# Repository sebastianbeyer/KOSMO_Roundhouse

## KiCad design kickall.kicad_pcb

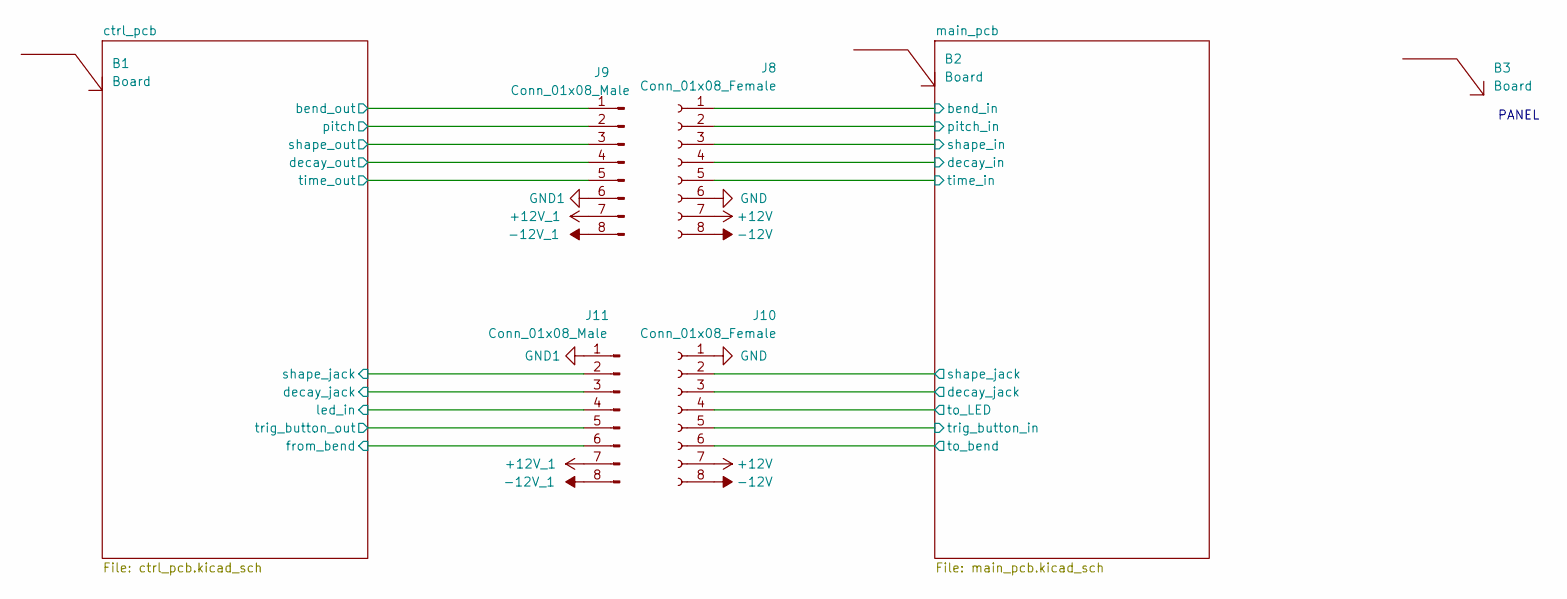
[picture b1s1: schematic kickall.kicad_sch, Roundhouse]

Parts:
B1, B2, B3: Board; Board_Marker
J8, J10: Conn_01x08_Female; PinSocket_1x08_P2.54mm_Vertical
J9, J11: Conn_01x08_Male; PinHeader_1x08_P2.54mm_Vertical

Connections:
+12V: J8.7, J10.7; also elsewhere on the board
+12V_1: J9.7, J11.7; also elsewhere on the board
-12V: J8.8, J10.8; also elsewhere on the board
-12V_1: J9.8, J11.8; also elsewhere on the board
/ctrl_pcb/bend_out: J9.1; also elsewhere on the board
/ctrl_pcb/decay_jack: J11.3; also elsewhere on the board
/ctrl_pcb/decay_out: J9.4; also elsewhere on the board
/ctrl_pcb/from_bend: J11.6; also elsewhere on the board
/ctrl_pcb/led_in: J11.4; also elsewhere on the board
/ctrl_pcb/pitch: J9.2; also elsewhere on the board
/ctrl_pcb/shape_jack: J11.2; also elsewhere on the board
/ctrl_pcb/shape_out: J9.3; also elsewhere on the board
/ctrl_pcb/time_out: J9.5; also elsewhere on the board
/ctrl_pcb/trig_button_out: J11.5; also elsewhere on the board
/main_pcb/bend_in: J8.1; also elsewhere on the board
/main_pcb/decay_in: J8.4; also elsewhere on the board
/main_pcb/decay_jack: J10.3; also elsewhere on the board
/main_pcb/pitch_in: J8.2; also elsewhere on the board
/main_pcb/shape_in: J8.3; also elsewhere on the board
/main_pcb/shape_jack: J10.2; also elsewhere on the board
/main_pcb/time_in: J8.5; also elsewhere on the board
/main_pcb/to_LED: J10.4; also elsewhere on the board
/main_pcb/to_bend: J10.6; also elsewhere on the board
/main_pcb/trig_button_in: J10.5; also elsewhere on the board
GND: J8.6, J10.1; also elsewhere on the board
GND1: J9.6, J11.1; also elsewhere on the board

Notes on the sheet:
PANEL

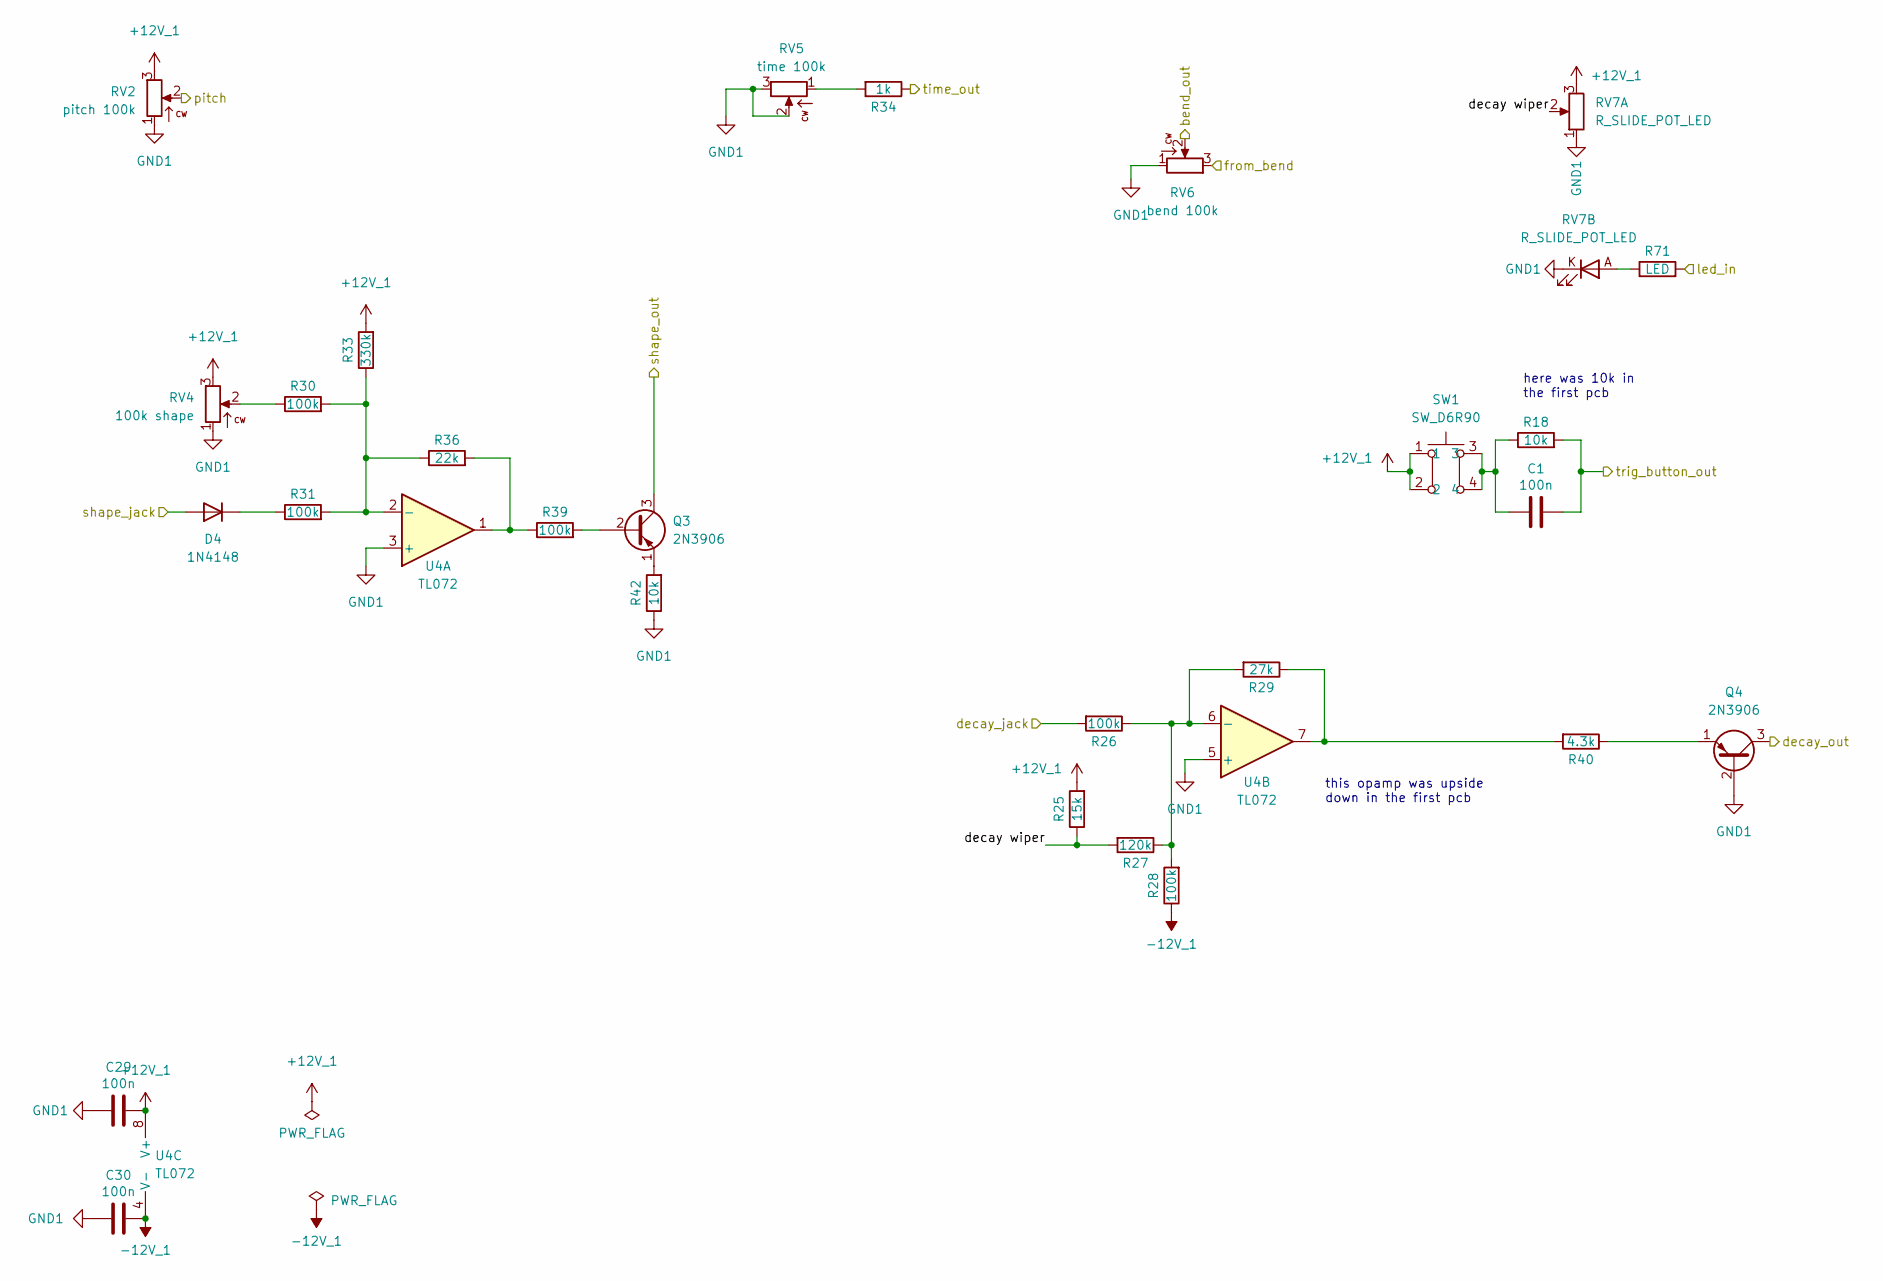
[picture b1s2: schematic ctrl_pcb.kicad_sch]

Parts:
C1, C29, C30: 100n; C_Disc_D3.0mm_W1.6mm_P2.50mm
D4: 1N4148; D_DO-35_SOD27_P7.62mm_Horizontal
Q3, Q4: 2N3906; TO-92_Inline_Wide
R18, R42: 10k; R_Axial_DIN0207_L6.3mm_D2.5mm_P10.16mm_Horizontal
R25: 15k; R_Axial_DIN0207_L6.3mm_D2.5mm_P10.16mm_Horizontal
R26, R28, R30, R31, R39: 100k; R_Axial_DIN0207_L6.3mm_D2.5mm_P10.16mm_Horizontal
R27: 120k; R_Axial_DIN0207_L6.3mm_D2.5mm_P10.16mm_Horizontal
R29: 27k; R_Axial_DIN0207_L6.3mm_D2.5mm_P10.16mm_Horizontal
R33: 330k; R_Axial_DIN0207_L6.3mm_D2.5mm_P10.16mm_Horizontal
R34: 1k; R_Axial_DIN0207_L6.3mm_D2.5mm_P10.16mm_Horizontal
R36: 22k; R_Axial_DIN0207_L6.3mm_D2.5mm_P10.16mm_Horizontal
R40: 4.3k; R_Axial_DIN0207_L6.3mm_D2.5mm_P10.16mm_Horizontal
R71: LED; R_Axial_DIN0207_L6.3mm_D2.5mm_P10.16mm_Horizontal
RV2: pitch 100k; Potentiometer_Alpha_RD901F-40-00D_Single_Vertical_centered
RV4: 100k shape; Potentiometer_Alpha_RD901F-40-00D_Single_Vertical_centered
RV5: time 100k; Potentiometer_Alpha_RD901F-40-00D_Single_Vertical_centered
RV6: bend 100k; Potentiometer_Alpha_RD901F-40-00D_Single_Vertical_centered
RV7: R_SLIDE_POT_LED; Potentiometer_Bourns_PTL6015_Single_Slide_LED_walpha
SW1: SW_D6R90; SW_D6R90_F1_LFS
U4: TL072; DIP-8_W7.62mm_Socket_LongPads

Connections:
+12V_1: C29.2, R25.2, R33.2, RV2.3, RV4.3, RV7.3, SW1.1, SW1.2, U4.8 (V+); also elsewhere on the board
-12V_1: C30.2, R28.1, U4.4 (V-); also elsewhere on the board
/ctrl_pcb/bend_out: RV6.2; also elsewhere on the board
/ctrl_pcb/decay wiper: R25.1, R27.2, RV7.2
/ctrl_pcb/decay_jack: R26.2; also elsewhere on the board
/ctrl_pcb/decay_out: Q4.3 (C); also elsewhere on the board
/ctrl_pcb/from_bend: RV6.3; also elsewhere on the board
/ctrl_pcb/led_in: R71.2; also elsewhere on the board
/ctrl_pcb/pitch: RV2.2; also elsewhere on the board
/ctrl_pcb/shape_jack: D4.2 (A); also elsewhere on the board
/ctrl_pcb/shape_out: Q3.3 (C); also elsewhere on the board
/ctrl_pcb/time_out: R34.1; also elsewhere on the board
/ctrl_pcb/trig_button_out: C1.2, R18.2; also elsewhere on the board
GND1: C29.1, C30.1, Q4.2 (B), R42.1, RV2.1, RV4.1, RV5.2, RV5.3, RV6.1, RV7.1, RV7.K, U4.3 (+), U4.5 (+); also elsewhere on the board
unnamed: C1.1, R18.1, SW1.3, SW1.4
unnamed: D4.1 (K), R31.1
unnamed: Q3.1 (E), R42.2
unnamed: Q3.2 (B), R39.2
unnamed: Q4.1 (E), R40.1
unnamed: R26.1, R27.1, R28.2, R29.2, U4.6 (-)
unnamed: R29.1, R40.2, U4.7
unnamed: R30.1, RV4.2
unnamed: R30.2, R31.2, R33.1, R36.1, U4.2 (-)
unnamed: R34.2, RV5.1
unnamed: R36.2, R39.1, U4.1
unnamed: R71.1, RV7.A

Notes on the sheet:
here was 10k in the first pcb
this opamp was upside down in the first pcb

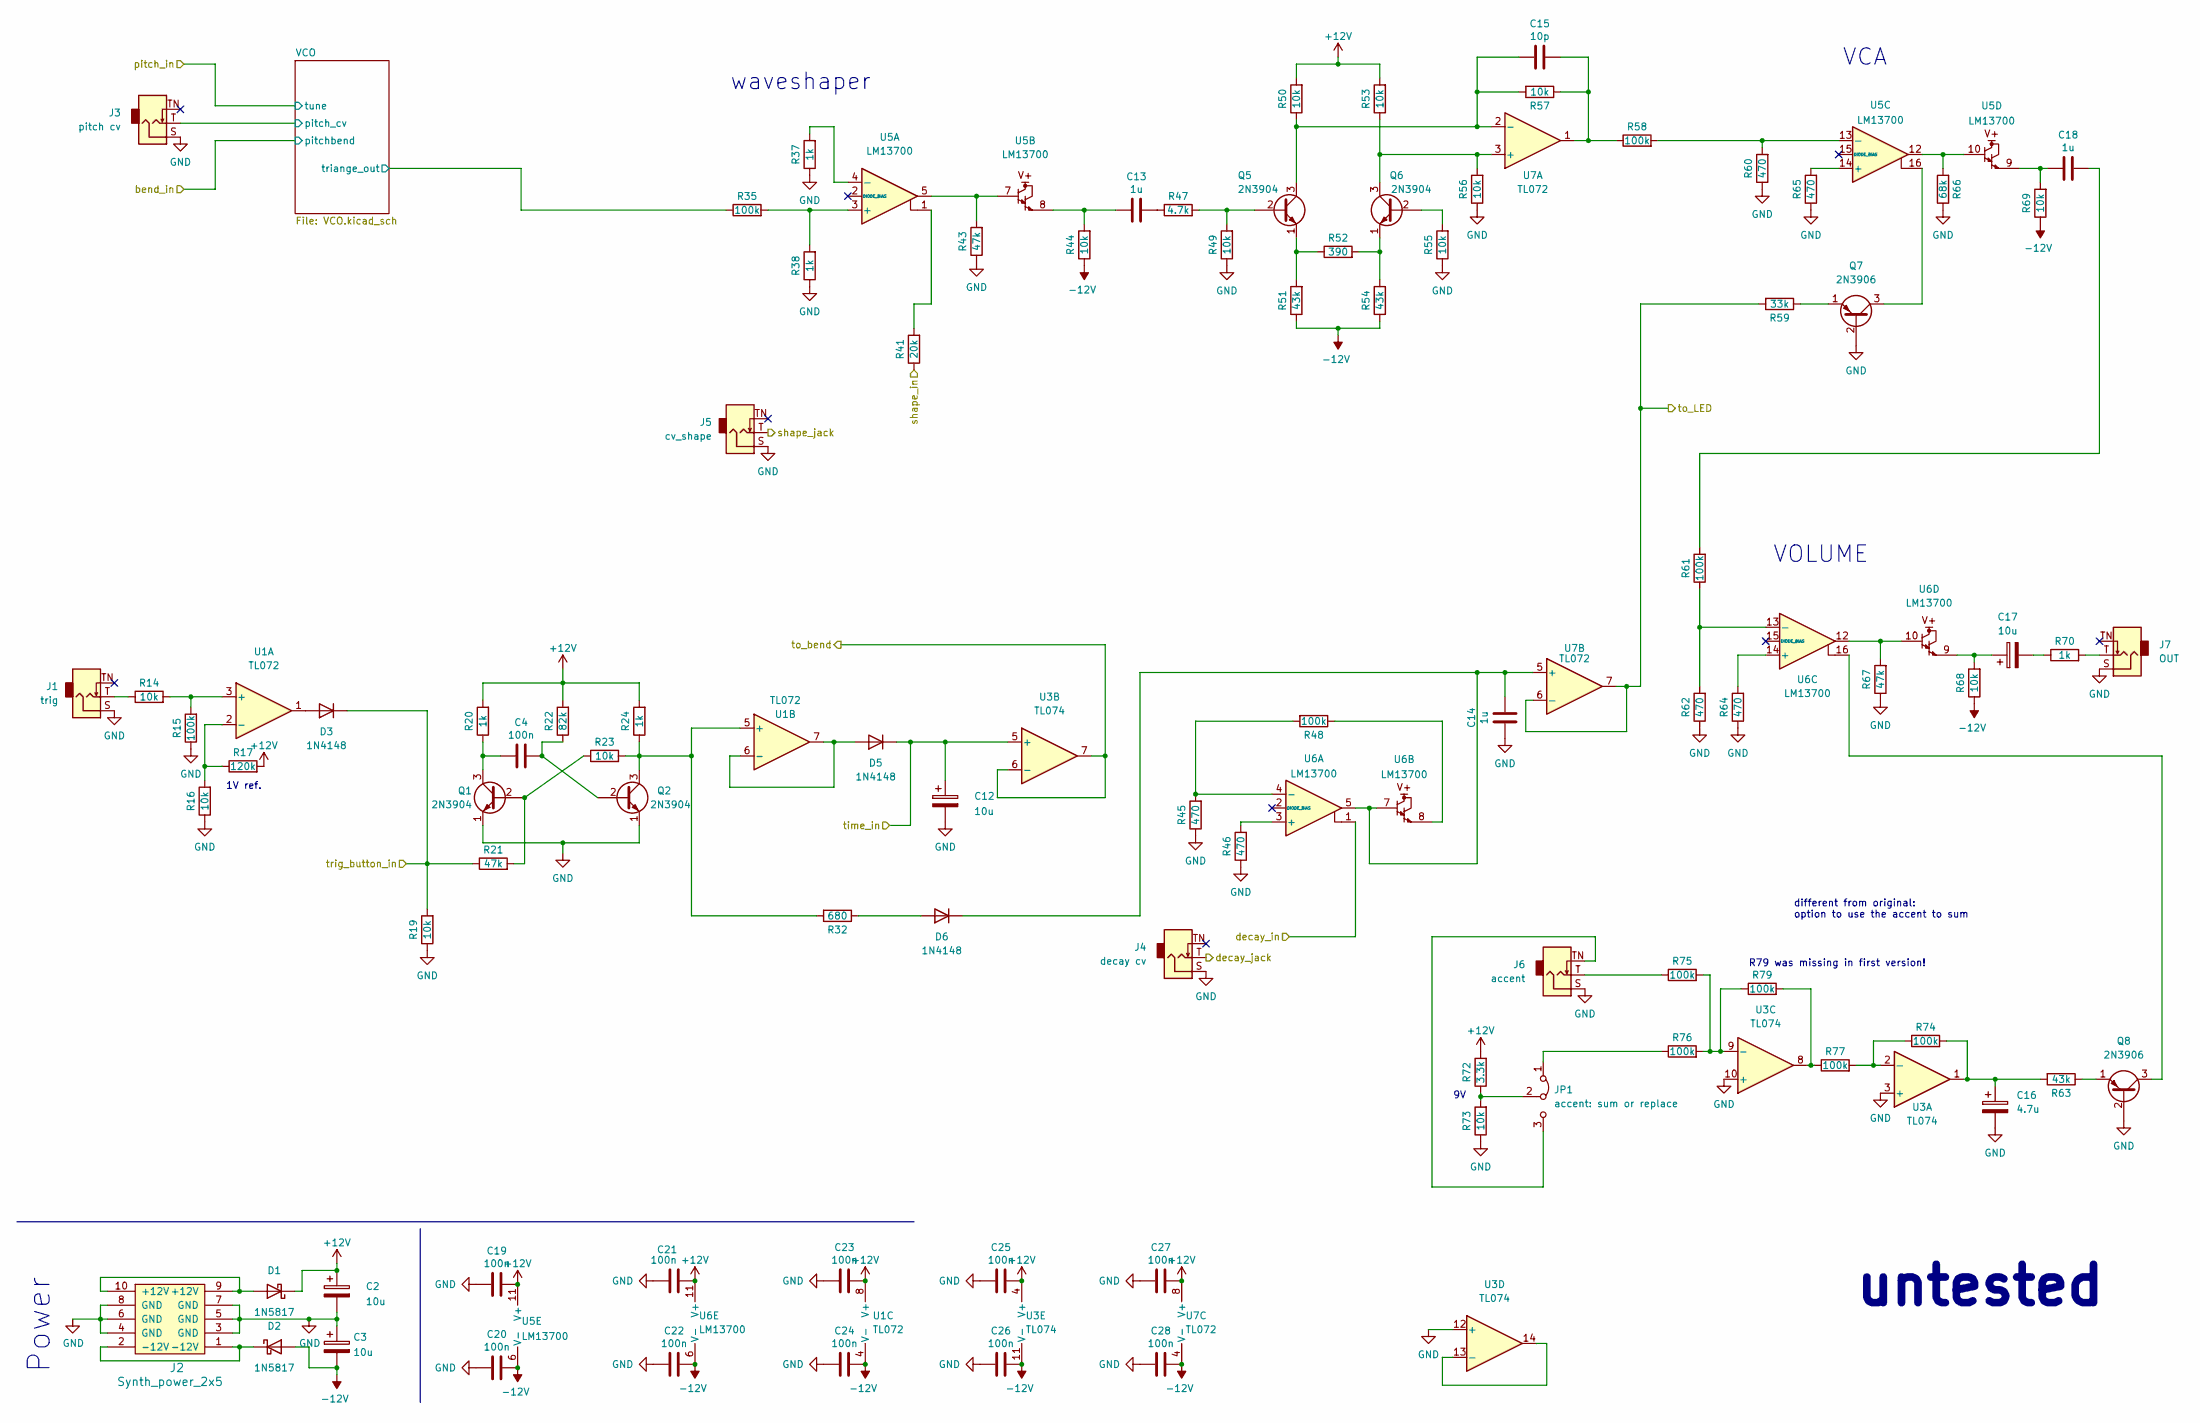
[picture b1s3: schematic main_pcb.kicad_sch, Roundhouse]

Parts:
C2, C3, C12, C17: 10u; CP_Radial_horizontalflat_D5mm_P2.50mm_H10mm_south
C4, C19, C20, C21, C22, C23, C24, C25, C26, C27, C28: 100n; C_Disc_D3.0mm_W1.6mm_P2.50mm
C13, C14, C18: 1u; C_Rect_L7.2mm_W7.2mm_P5.00mm_FKS2_FKP2_MKS2_MKP2
C15: 10p; C_Disc_D3.0mm_W1.6mm_P2.50mm
C16: 4.7u; CP_Radial_horizontalflat_D5mm_P2.50mm_H10mm_south
D1, D2: 1N5817; D_DO-41_SOD81_P10.16mm_Horizontal
D3, D5, D6: 1N4148; D_DO-35_SOD27_P7.62mm_Horizontal
J1: trig; Jack_6.35mm_PJ_629HAN_slots
J2: Synth_power_2x5; Power_Header
J3: pitch cv; Jack_6.35mm_PJ_629HAN_slots
J4: decay cv; Jack_6.35mm_PJ_629HAN_slots
J5: cv_shape; Jack_6.35mm_PJ_629HAN_slots
J6: accent; Jack_6.35mm_PJ_629HAN_slots
J7: OUT; Jack_6.35mm_PJ_629HAN_slots
JP1: accent: sum or replace; PinHeader_1x03_P2.54mm_Vertical
Q1, Q2, Q5, Q6: 2N3904; TO-92_Inline_Wide
Q7, Q8: 2N3906; TO-92_Inline_Wide
R14, R16, R19, R23, R44, R49, R50, R53, R55, R56, R57, R68, R69, R73: 10k; R_Axial_DIN0207_L6.3mm_D2.5mm_P10.16mm_Horizontal
R15, R35, R48, R58, R61, R74, R75, R76, R77, R79: 100k; R_Axial_DIN0207_L6.3mm_D2.5mm_P10.16mm_Horizontal
R17: 120k; R_Axial_DIN0207_L6.3mm_D2.5mm_P10.16mm_Horizontal
R20, R24, R37, R38, R70: 1k; R_Axial_DIN0207_L6.3mm_D2.5mm_P10.16mm_Horizontal
R21, R43, R67: 47k; R_Axial_DIN0207_L6.3mm_D2.5mm_P10.16mm_Horizontal
R22: 82k; R_Axial_DIN0207_L6.3mm_D2.5mm_P10.16mm_Horizontal
R32: 680; R_Axial_DIN0207_L6.3mm_D2.5mm_P10.16mm_Horizontal
R41: 20k; R_Axial_DIN0207_L6.3mm_D2.5mm_P10.16mm_Horizontal
R45, R46, R60, R62, R64, R65: 470; R_Axial_DIN0207_L6.3mm_D2.5mm_P10.16mm_Horizontal
R47: 4.7k; R_Axial_DIN0207_L6.3mm_D2.5mm_P10.16mm_Horizontal
R51, R54, R63: 43k; R_Axial_DIN0207_L6.3mm_D2.5mm_P10.16mm_Horizontal
R52: 390; R_Axial_DIN0207_L6.3mm_D2.5mm_P10.16mm_Horizontal
R59: 33k; R_Axial_DIN0207_L6.3mm_D2.5mm_P10.16mm_Horizontal
R66: 68k; R_Axial_DIN0207_L6.3mm_D2.5mm_P10.16mm_Horizontal
R72: 3.3k; R_Axial_DIN0207_L6.3mm_D2.5mm_P10.16mm_Horizontal
U1, U7: TL072; DIP-8_W7.62mm_Socket_LongPads
U3: TL074; DIP-14_W7.62mm_Socket_LongPads
U5, U6: LM13700; DIP-16_W7.62mm_Socket_LongPads

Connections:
+12V: C2.1, C19.2, C21.2, C23.2, C25.2, C27.2, D1.1 (K), R17.2, R20.2, R22.2, R24.2, R50.2, R53.2, R72.2, U1.8 (V+), U3.4 (V+), U5.11 (V+), U6.11 (V+), U7.8 (V+); also elsewhere on the board
-12V: C3.2, C20.2, C22.2, C24.2, C26.2, C28.2, D2.2 (A), R44.1, R51.1, R54.1, R68.1, R69.1, U1.4 (V-), U3.11 (V-), U5.6 (V-), U6.6 (V-), U7.4 (V-); also elsewhere on the board
/main_pcb/VCO/pitch_cv: J3.T; also elsewhere on the board
/main_pcb/VCO/triange_out: R35.1; also elsewhere on the board
/main_pcb/decay_in: U6.1; also elsewhere on the board
/main_pcb/decay_jack: J4.T; also elsewhere on the board
/main_pcb/shape_in: R41.1; also elsewhere on the board
/main_pcb/shape_jack: J5.T; also elsewhere on the board
/main_pcb/time_in: C12.1, D5.1 (K), U3.5 (+); also elsewhere on the board
/main_pcb/to_LED: R59.2, U7.6 (-), U7.7; also elsewhere on the board
/main_pcb/to_bend: U3.6 (-), U3.7; also elsewhere on the board
/main_pcb/trig_button_in: D3.1 (K), R19.2, R21.1; also elsewhere on the board
GND: C2.2, C3.1, C12.2, C14.1, C16.2, C19.1, C20.1, C21.1, C22.1, C23.1, C24.1, C25.1, C26.1, C27.1, C28.1, J1.S, J2.3 (GND), J2.4 (GND), J2.5 (GND), J2.6 (GND), J2.7 (GND), J2.8 (GND), J3.S, J4.S, J5.S, J6.S, J7.S, Q1.1 (E), Q2.1 (E), Q7.2 (B), Q8.2 (B), R15.1, R16.1, R19.1, R37.1, R38.1, R43.1, R45.1, R46.1, R49.1, R55.1, R56.1, R60.1, R62.1, R64.1, R65.1, R66.1, R67.1, R73.1, U3.3 (+), U3.10 (+), U3.12 (+); also elsewhere on the board
unnamed: C4.1, Q1.3 (C), R20.1
unnamed: C4.2, Q2.2 (B), R22.1
unnamed: C13.1, R44.2, U5.8
unnamed: C13.2, R47.1
unnamed: C14.2, D6.1 (K), U6.5, U6.7, U7.5 (+)
unnamed: C15.1, Q5.3 (C), R50.1, R57.2, U7.2 (-)
unnamed: C15.2, R57.1, R58.1, U7.1
unnamed: C16.1, R63.2, R74.2, U3.1
unnamed: C17.1, R68.2, U6.9
unnamed: C17.2, R70.1
unnamed: C18.1, R69.2, U5.9
unnamed: C18.2, R61.2
unnamed: D1.2 (A), J2.9 (+12V), J2.10 (+12V)
unnamed: D2.1 (K), J2.1 (-12V), J2.2 (-12V)
unnamed: D3.2 (A), U1.1
unnamed: D5.2 (A), U1.6 (-), U1.7
unnamed: D6.2 (A), R32.1
unnamed: J1.T, R14.1
unnamed: J6.T, R75.1
unnamed: J6.TN, JP1.3 (B)
unnamed: J7.T, R70.2
unnamed: JP1.1 (A), R76.1
unnamed: JP1.2 (C), R72.1, R73.2
unnamed: Q1.2 (B), R21.2, R23.1
unnamed: Q2.3 (C), R23.2, R24.1, R32.2, U1.5 (+)
unnamed: Q5.1 (E), R51.2, R52.1
unnamed: Q5.2 (B), R47.2, R49.2
unnamed: Q6.1 (E), R52.2, R54.2
unnamed: Q6.2 (B), R55.2
unnamed: Q6.3 (C), R53.1, R56.2, U7.3 (+)
unnamed: Q7.1 (E), R59.1
unnamed: Q7.3 (C), U5.16
unnamed: Q8.1 (E), R63.1
unnamed: Q8.3 (C), U6.16
unnamed: R14.2, R15.2, U1.3 (+)
unnamed: R16.2, R17.1, U1.2 (-)
unnamed: R35.2, R38.2, U5.3 (+)
unnamed: R37.2, U5.4 (-)
unnamed: R41.2, U5.1
unnamed: R43.2, U5.5, U5.7
unnamed: R45.2, R48.2, U6.4 (-)
unnamed: R46.2, U6.3 (+)
unnamed: R48.1, U6.8
unnamed: R58.2, R60.2, U5.13 (-)
unnamed: R61.1, R62.2, U6.13 (-)
unnamed: R64.2, U6.14 (+)
unnamed: R65.2, U5.14 (+)
unnamed: R66.2, U5.10, U5.12
unnamed: R67.2, U6.10, U6.12
unnamed: R74.1, R77.2, U3.2 (-)
unnamed: R75.2, R76.2, R79.1, U3.9 (-)
unnamed: R77.1, R79.2, U3.8
unnamed: U3.13 (-), U3.14

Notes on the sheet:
different from original: option to use the accent to sum
R79 was missing in first version!
1V ref.
waveshaper
VCA
VOLUME
untested
Power

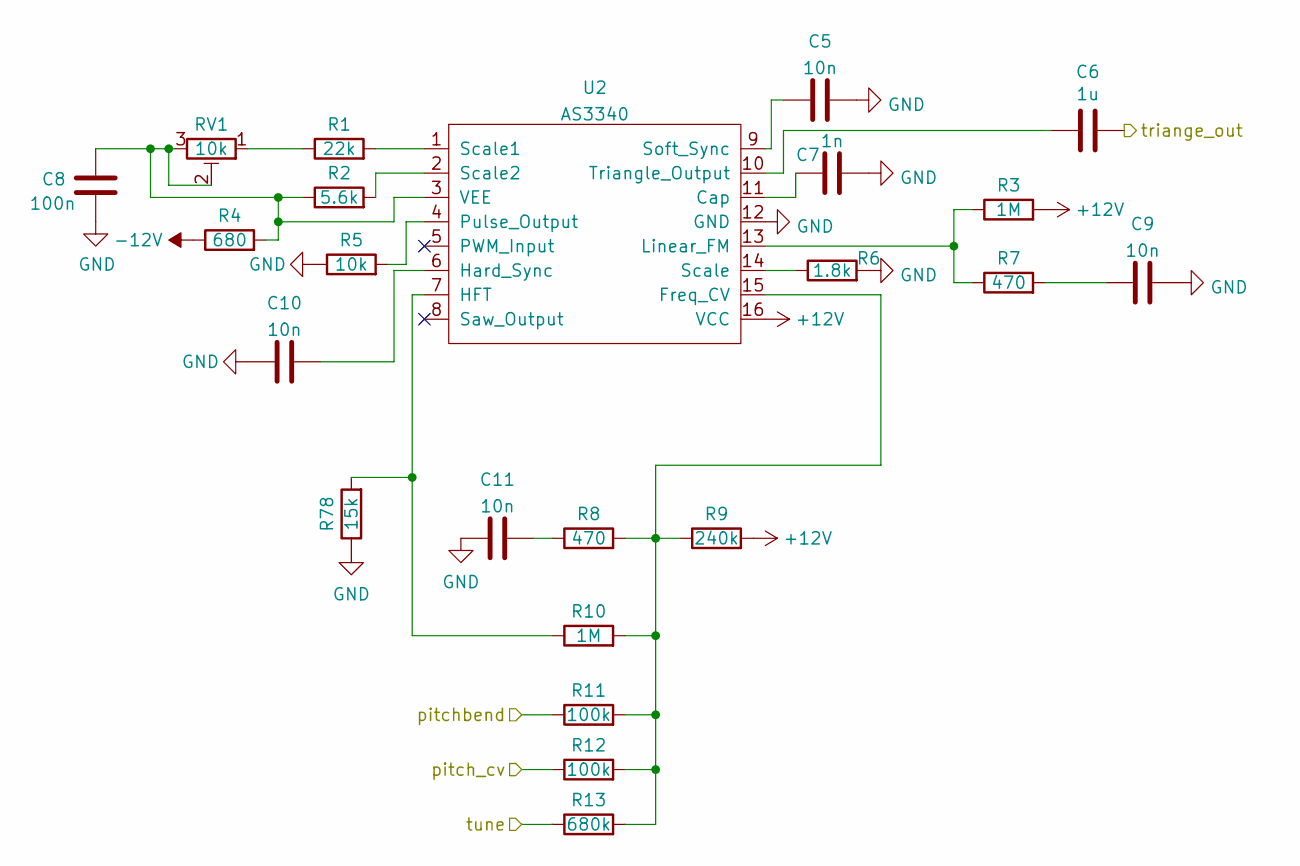
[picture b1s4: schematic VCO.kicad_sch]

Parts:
C5, C9, C10, C11: 10n; C_Disc_D3.0mm_W1.6mm_P2.50mm
C6: 1u; C_Rect_L7.2mm_W7.2mm_P5.00mm_FKS2_FKP2_MKS2_MKP2
C7: 1n; C_Disc_D3.0mm_W1.6mm_P2.50mm
C8: 100n; C_Disc_D3.0mm_W1.6mm_P2.50mm
R1: 22k; R_Axial_DIN0207_L6.3mm_D2.5mm_P10.16mm_Horizontal
R2: 5.6k; R_Axial_DIN0207_L6.3mm_D2.5mm_P10.16mm_Horizontal
R3, R10: 1M; R_Axial_DIN0207_L6.3mm_D2.5mm_P10.16mm_Horizontal
R4: 680; R_Axial_DIN0207_L6.3mm_D2.5mm_P10.16mm_Horizontal
R5: 10k; R_Axial_DIN0207_L6.3mm_D2.5mm_P10.16mm_Horizontal
R6: 1.8k; R_Axial_DIN0207_L6.3mm_D2.5mm_P10.16mm_Horizontal
R7, R8: 470; R_Axial_DIN0207_L6.3mm_D2.5mm_P10.16mm_Horizontal
R9: 240k; R_Axial_DIN0207_L6.3mm_D2.5mm_P10.16mm_Horizontal
R11, R12: 100k; R_Axial_DIN0207_L6.3mm_D2.5mm_P10.16mm_Horizontal
R13: 680k; R_Axial_DIN0207_L6.3mm_D2.5mm_P10.16mm_Horizontal
R78: 15k; R_Axial_DIN0207_L6.3mm_D2.5mm_P10.16mm_Horizontal
RV1: 10k; Potentiometer_Bourns_3296Z_Horizontal
U2: AS3340; DIP-16_W7.62mm_Socket_LongPads

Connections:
+12V: R3.2, R9.2, U2.16 (VCC); also elsewhere on the board
-12V: R4.1; also elsewhere on the board
/main_pcb/VCO/pitch_cv: R12.1; also elsewhere on the board
/main_pcb/VCO/triange_out: C6.2; also elsewhere on the board
/main_pcb/bend_in: R11.1; also elsewhere on the board
/main_pcb/pitch_in: R13.1; also elsewhere on the board
GND: C5.2, C7.2, C8.1, C9.2, C10.1, C11.1, R5.1, R6.2, R78.1, U2.12 (GND); also elsewhere on the board
unnamed: C5.1, U2.9 (Soft_Sync)
unnamed: C6.1, U2.10 (Triangle_Output)
unnamed: C7.1, U2.11 (Cap)
unnamed: C8.2, R2.1, R4.2, RV1.2, RV1.3, U2.3 (VEE)
unnamed: C9.1, R7.2
unnamed: C10.2, U2.6 (Hard_Sync)
unnamed: C11.2, R8.1
unnamed: R1.1, RV1.1
unnamed: R1.2, U2.1 (Scale1)
unnamed: R2.2, U2.2 (Scale2)
unnamed: R3.1, R7.1, U2.13 (Linear_FM)
unnamed: R5.2, U2.4 (Pulse_Output)
unnamed: R6.1, U2.14 (Scale)
unnamed: R10.1, R78.2, U2.7 (HFT)
unnamed: R8.2, R9.1, R10.2, R11.2, R12.2, R13.2, U2.15 (Freq_CV)

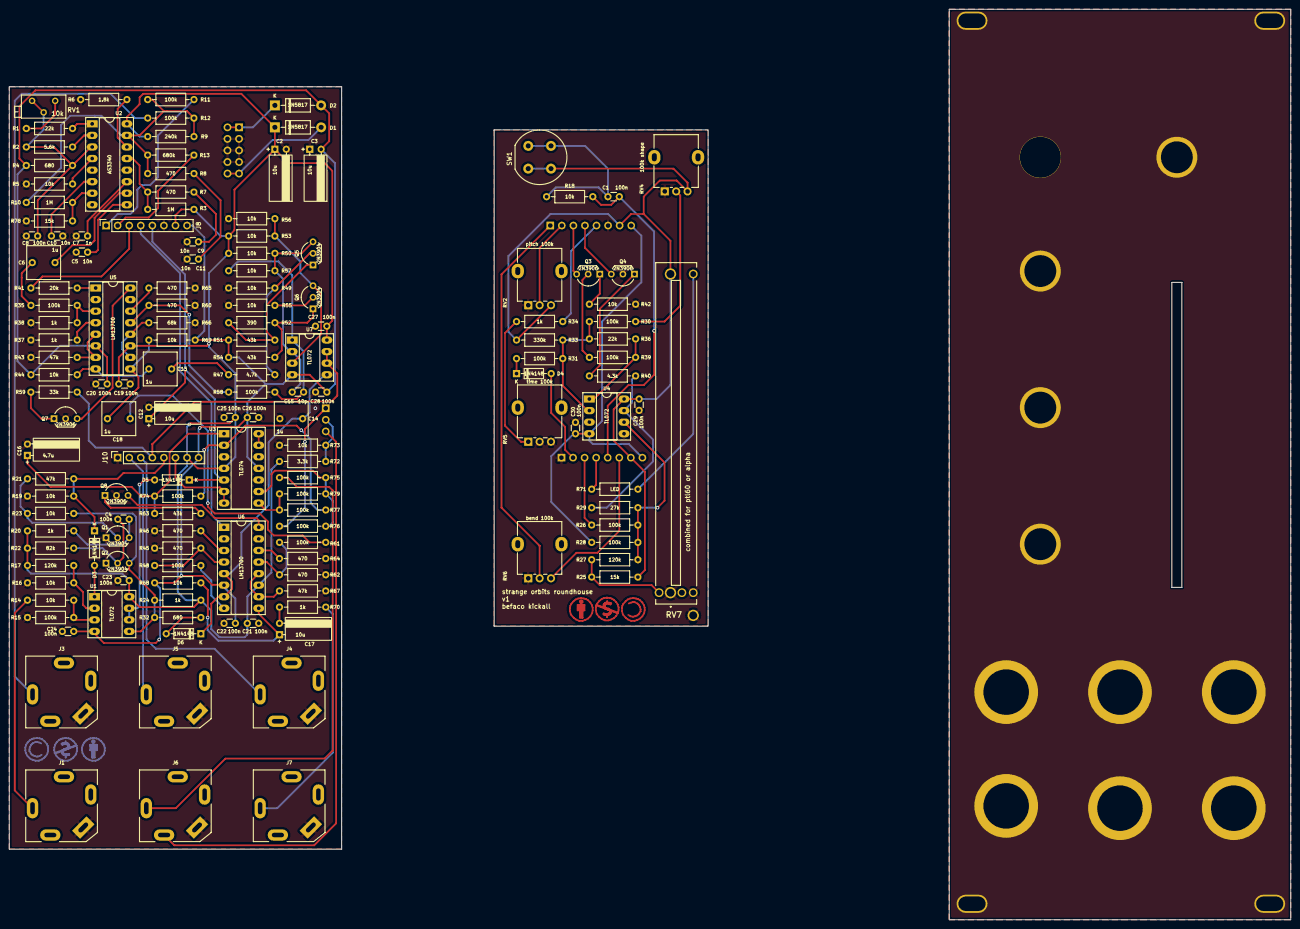
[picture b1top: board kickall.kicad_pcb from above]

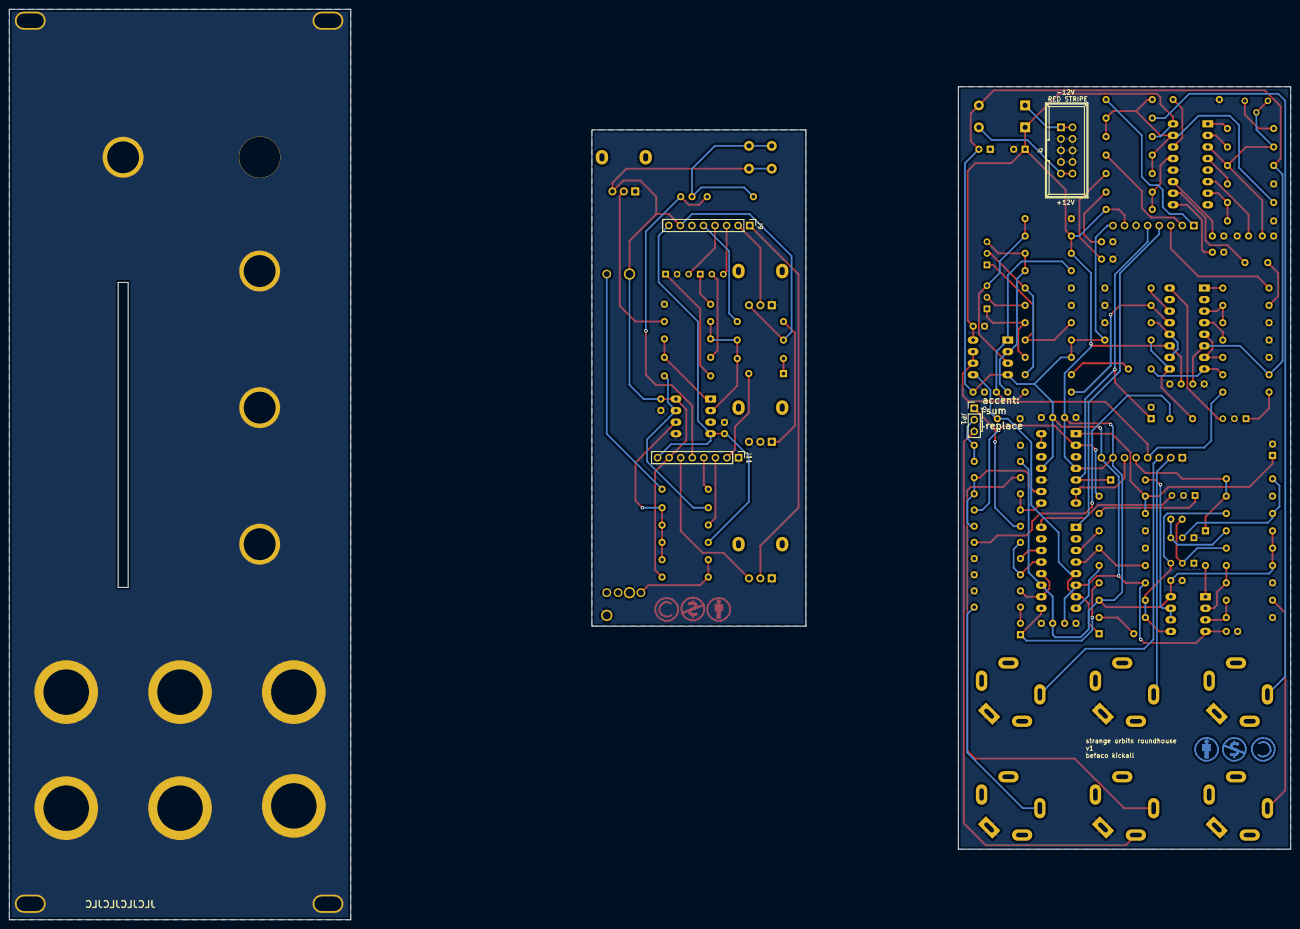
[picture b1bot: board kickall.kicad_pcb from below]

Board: 2 copper layers, 281.5 x 200.0 mm, 158 parts (7 on the bottom side), 109 nets.

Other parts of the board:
 : Symbol_CC-ShareAlike_CopperTop_Small
  : Symbol_CC-Attribution_CopperTop_Small
  #2: Symbol_CC-ShareAlike_CopperTop_Small
  #3: Symbol_CC-Noncommercial_CopperTop_Small
  #4: Symbol_CC-Attribution_CopperTop_Small
 #2: Symbol_CC-Noncommercial_CopperTop_Small

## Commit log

2022-11-15 initial
2022-11-23 fix opampon ctrl pcb, fix accent and make slide pot slot 0.2mm wider
